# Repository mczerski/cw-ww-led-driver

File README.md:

# cw-ww-led-driver

Double Led Driver using CAT4101 IC.

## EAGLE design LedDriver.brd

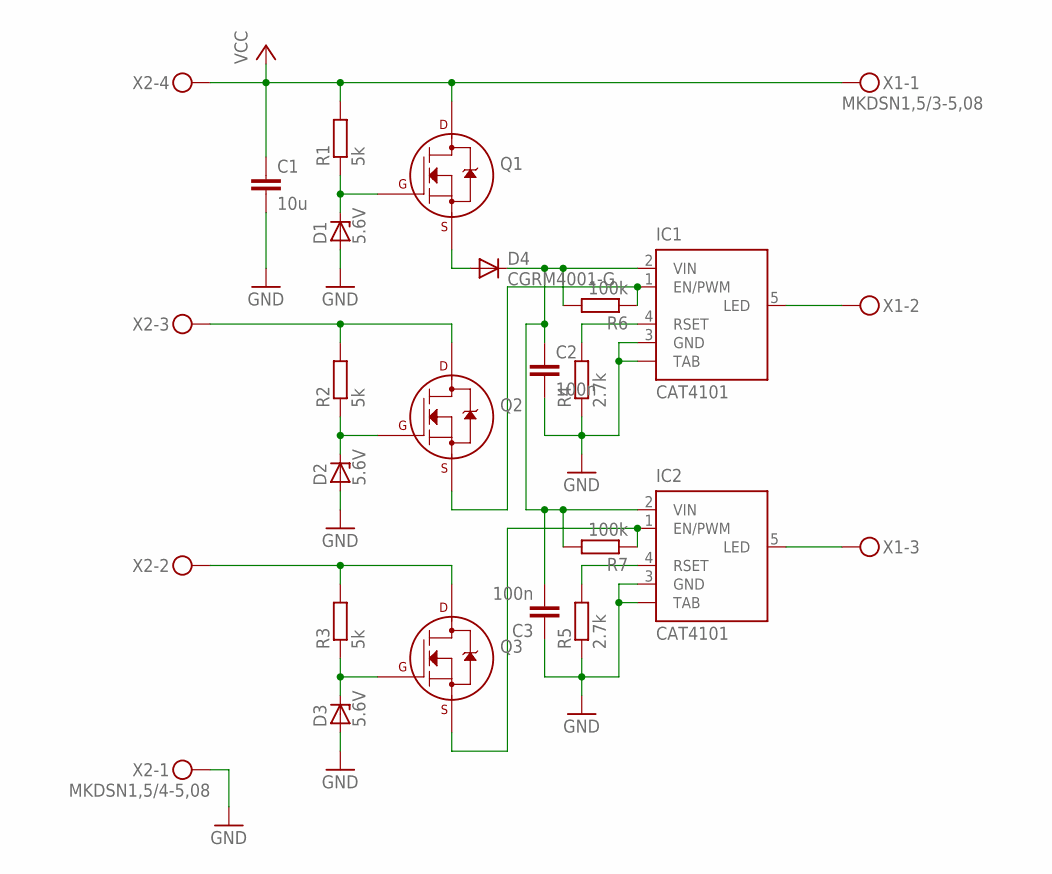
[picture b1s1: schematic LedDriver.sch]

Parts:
C1: 10u; C1210
C2, C3: 100n; C0402
D1, D2, D3: 5.6V; SOD80C
D4: CGRM4001-G; SOD-123_MINI-SMA
IC1, IC2: CAT4101; TO263_5
Q1, Q2, Q3: 2N7002_SOT23; SOT-23
R1, R2, R3: 5k; R0603
R4, R5: 2.7k; R0603
R6, R7: 100k; R0603
X1: MKDSN1,5/3-5,08
X2: MKDSN1,5/4-5,08

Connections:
GND: C1.2, C2.2, C3.1, D1.A, D2.A, D3.A, IC1.3 (GND), IC1.TAB, IC2.3 (GND), IC2.TAB, R4.1, R5.1, X2.1
unnamed: D1.C, Q1.1 (G), R1.1
unnamed: D4.A, Q1.2 (S)
unnamed: Q2.3 (D), R2.2, X2.3
unnamed: D2.C, Q2.1 (G), R2.1
unnamed: Q3.3 (D), R3.2, X2.2
unnamed: D3.C, Q3.1 (G), R3.1
unnamed: IC1.1 (EN/PWM), Q2.2 (S), R6.1
unnamed: IC2.1 (EN/PWM), Q3.2 (S), R7.1
unnamed: C2.1, C3.2, D4.C, IC1.2 (VIN), IC2.2 (VIN), R6.2, R7.2
unnamed: IC2.4 (RSET), R5.2
unnamed: IC1.4 (RSET), R4.2
unnamed: IC1.5 (LED), X1.2
unnamed: IC2.5 (LED), X1.3
VCC: C1.1, Q1.3 (D), R1.2, X1.1, X2.4

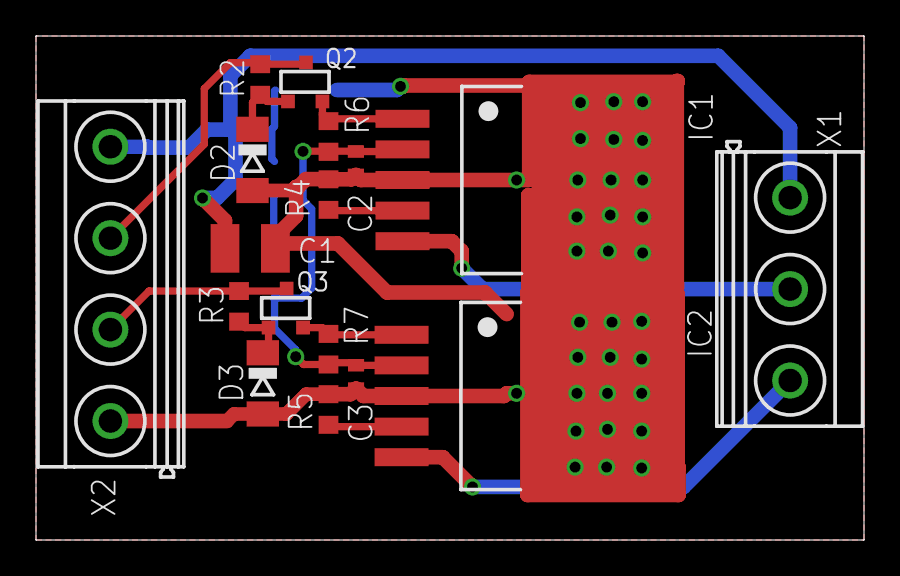
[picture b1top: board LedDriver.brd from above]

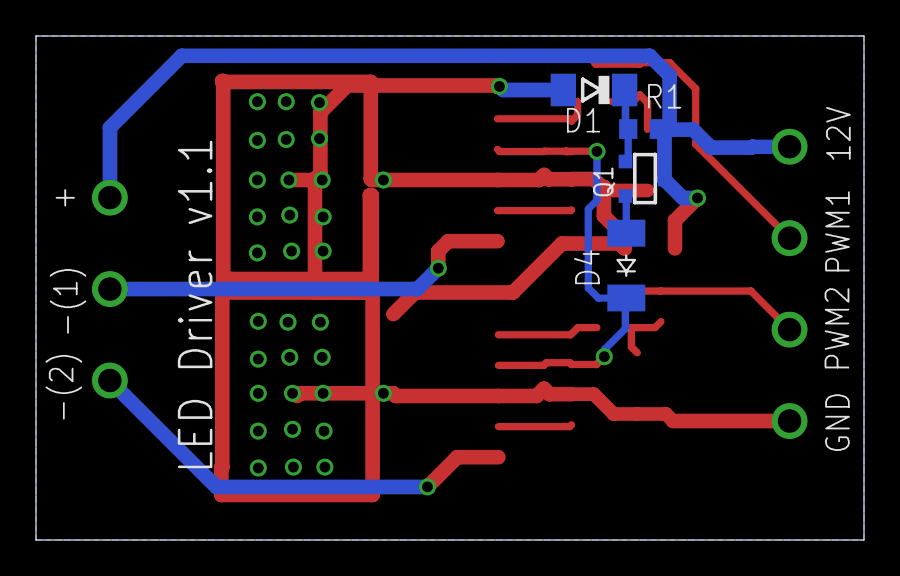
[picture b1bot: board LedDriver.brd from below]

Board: 2 copper layers, 46.0 x 28.0 mm, 21 parts (4 on the bottom side), 15 nets.

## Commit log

2017-09-22 vwersion 1.0
2017-10-24 added pull up resistors for enable pin
2017-10-28 added reverse polarity protection diode
